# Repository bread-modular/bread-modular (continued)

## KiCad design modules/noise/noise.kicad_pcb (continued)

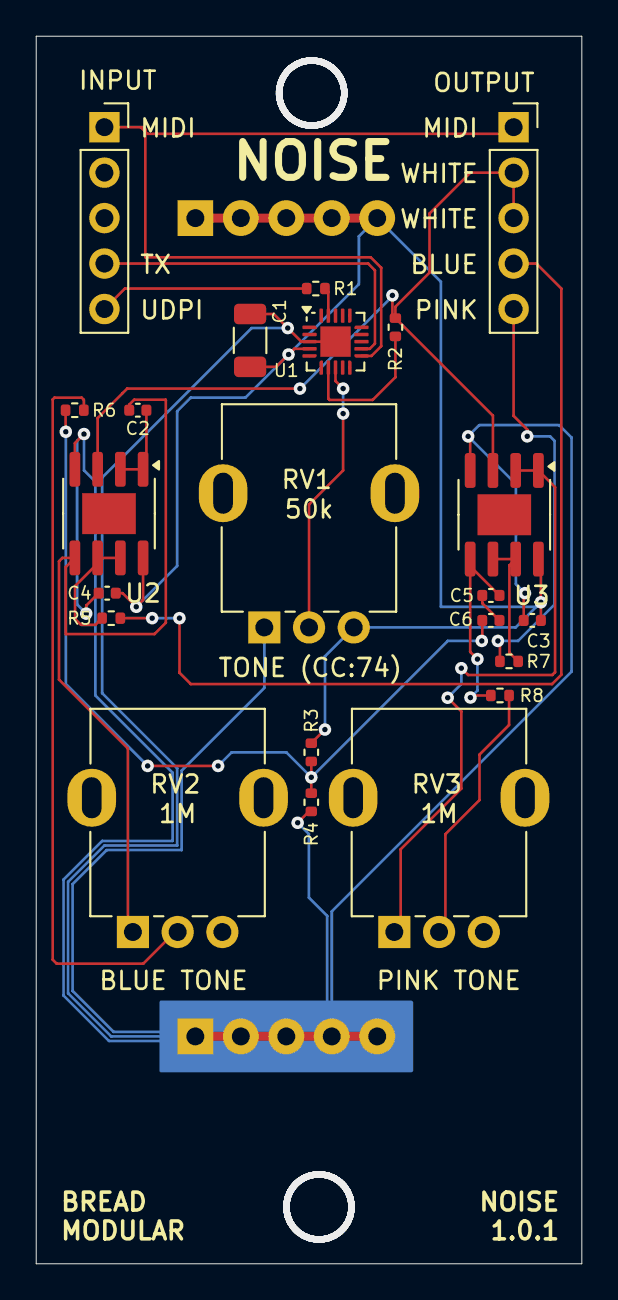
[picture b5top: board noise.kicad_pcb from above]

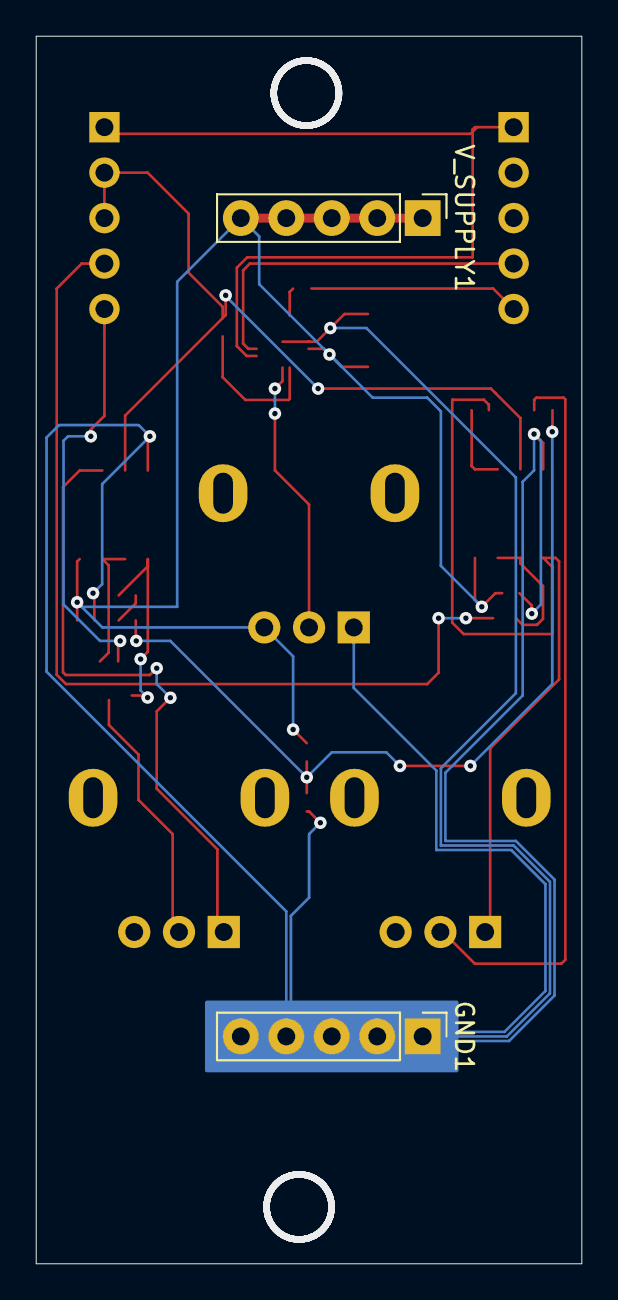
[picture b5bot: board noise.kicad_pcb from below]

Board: 2 copper layers, 30.5 x 68.6 mm, 24 parts (2 on the bottom side), 21 nets.

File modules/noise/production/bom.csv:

Designator,Footprint,Quantity,Value,LCSC Part #
C1,1206,1,100uf,
C2,0402,1,100pf,
"C3, C4",0402,2,100nf,
"C5, C6",0402,2,10nf,
"GND1, V_SUPPLY1",Power_Connector,2,Conn_01x05_Pin,
"INPUT1, OUTPUT1",PinSocket_1x05_P2.54mm_Vertical,2,Conn_01x05_Socket,
R1,0402,1,4.7k,
"R2, R3, R4, R5, R7",0402,5,1k,
R6,0402,1,330,
R8,0402,1,22k,
RV1,Potentiometer_RV09,1,50k,
"RV2, RV3",Potentiometer_RV09,2,1M,
U1,VQFN-20-1EP_3x3mm_P0.4mm_EP1.7x1.7mm,1,ATtiny1616-M,
"U2, U3",SOIC-8-1EP_3.9x4.9mm_P1.27mm_EP2.29x3mm,2,MCP6002-xSN,

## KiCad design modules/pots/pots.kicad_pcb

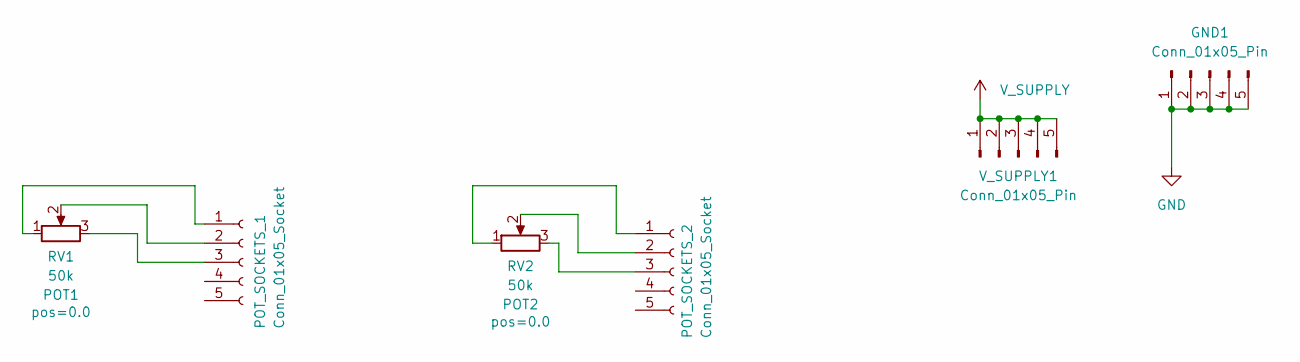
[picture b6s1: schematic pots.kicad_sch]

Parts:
GND1: Conn_01x05_Pin; Power_Connector
POT_SOCKETS_1, POT_SOCKETS_2: Conn_01x05_Socket; PinSocket_1x05_P2.54mm_Vertical
RV1, RV2: 50k; Potentiometer_RV09
V_SUPPLY1: Conn_01x05_Pin; Power_Connector

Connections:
GND: GND1.1, GND1.2, GND1.3, GND1.4, GND1.5
unnamed: POT_SOCKETS_1.1, RV1.1
unnamed: POT_SOCKETS_1.2, RV1.2
unnamed: POT_SOCKETS_1.3, RV1.3
unnamed: POT_SOCKETS_2.1, RV2.1
unnamed: POT_SOCKETS_2.2, RV2.2
unnamed: POT_SOCKETS_2.3, RV2.3
V_SUPPLY: V_SUPPLY1.1, V_SUPPLY1.2, V_SUPPLY1.3, V_SUPPLY1.4, V_SUPPLY1.5

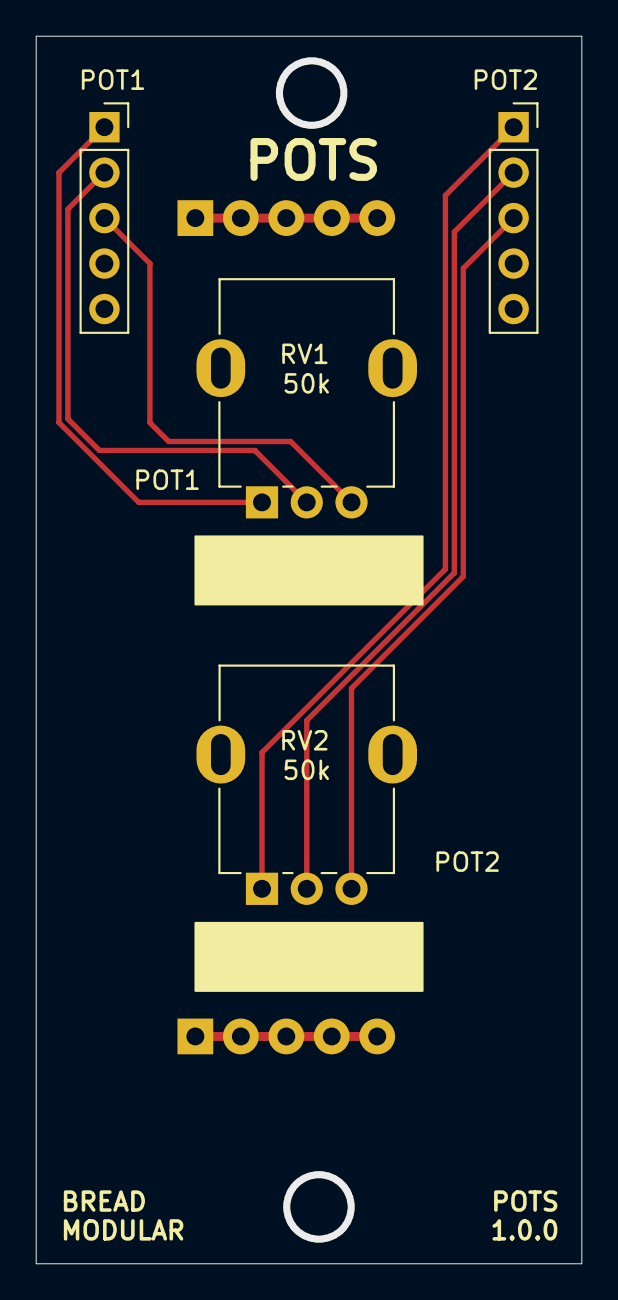
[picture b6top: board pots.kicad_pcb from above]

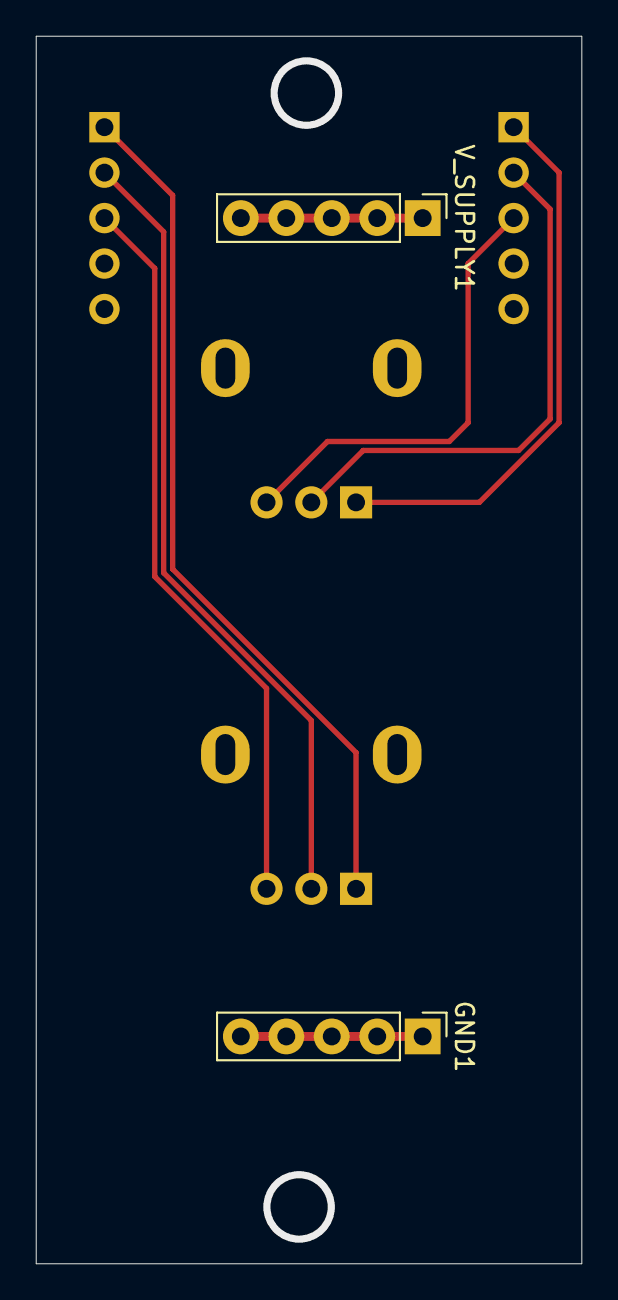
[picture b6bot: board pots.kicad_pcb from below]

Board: 2 copper layers, 30.5 x 68.6 mm, 6 parts (2 on the bottom side), 8 nets.

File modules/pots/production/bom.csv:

Designator,Footprint,Quantity,Value,LCSC Part #
"GND1, V_SUPPLY1",Power_Connector,2,Conn_01x05_Pin,
"POT_SOCKETS_1, POT_SOCKETS_2",PinSocket_1x05_P2.54mm_Vertical,2,Conn_01x05_Socket,
"RV1, RV2",Potentiometer_RV09,2,50k,

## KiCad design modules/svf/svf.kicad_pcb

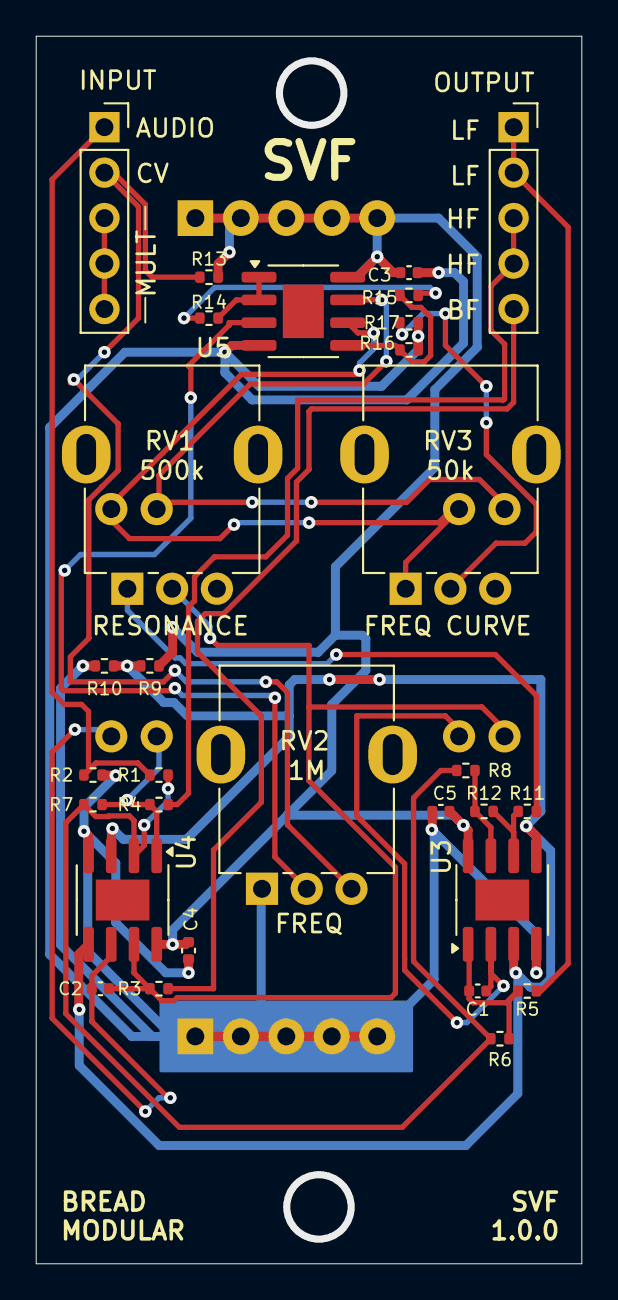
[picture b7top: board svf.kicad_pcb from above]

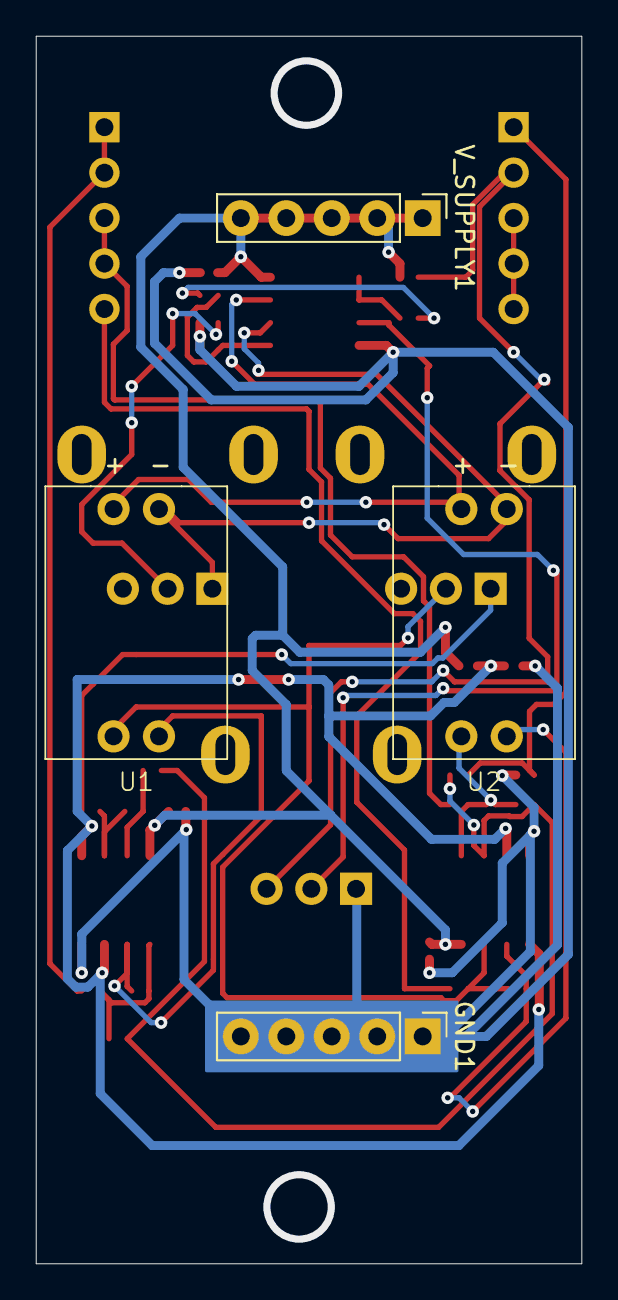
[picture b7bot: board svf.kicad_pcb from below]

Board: 2 copper layers, 30.5 x 68.6 mm, 34 parts (4 on the bottom side), 25 nets.

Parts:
C1, C2: 10nf; C_0402_1005Metric
C3, C4, C5: 0.1uf; C_0402_1005Metric
GND1: Conn_01x05_Pin; Power_Connector
INPUT1: Conn_01x05_Socket; PinSocket_1x05_P2.54mm_Vertical
OUTPUT1: Conn_01x05_Socket; PinSocket_1x05_P2.54mm_Vertical
R1, R11, R12: 51k; R_0402_1005Metric
R2: 22k; R_0402_1005Metric
R3, R4, R5, R9, R10, R14: 1k; R_0402_1005Metric
R6, R7, R8: 10k; R_0402_1005Metric
R13: 100k; R_0402_1005Metric
R15, R16: 1M; R_0402_1005Metric
R17: 5.1k; R_0402_1005Metric
RV1: 500k; Potentiometer_RV09
RV2: 1M; Potentiometer_RV09
RV3: 50k; Potentiometer_RV09
U1, U2: VTL5C
U3, U4, U5: MCP6002-xSN; SOIC-8-1EP_3.9x4.9mm_P1.27mm_EP2.29x3mm
V_SUPPLY1: Conn_01x05_Pin; Power_Connector

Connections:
GND: C3.2, C4.2, C5.2, GND1.1, GND1.2, GND1.3, GND1.4, GND1.5, R2.1, R10.2, R16.1, R17.1, RV2.1, U3.4 (V-), U4.4 (V-), U5.4 (V-)
unnamed: C1.2, R5.1, R6.1, U3.1
unnamed: C2.2, R3.1, RV1.2, U1.4, U4.7
unnamed: INPUT1.3, INPUT1.4, INPUT1.5
unnamed: R4.1, R7.2, U2.4, U4.1
unnamed: R11.2, RV1.1
unnamed: R8.1, R12.1, U3.7
unnamed: R14.1, R15.2
unnamed: R17.2, RV3.2
unnamed: C1.1, U1.3, U3.2 (-)
unnamed: R11.1, R12.2, U3.6 (-)
unnamed: R1.2, R6.2, R7.1, R8.2, U4.2 (-)
unnamed: C2.1, U2.3, U4.6 (-)
unnamed: RV2.2, U5.3 (+)
unnamed: R14.2, U5.1, U5.2 (-)
unnamed: R15.1, R16.2, U5.5 (+)
VACTROL_NEG: RV3.1, U1.1 (-), U2.1 (-), U5.6 (-)
VACTROL_POS: U1.2 (+), U2.2 (+), U5.7
V_BF: OUTPUT1.5, R3.2
V_CV: INPUT1.2, R13.1, RV2.3
V_HF: OUTPUT1.3, OUTPUT1.4, R4.2
V_IN: INPUT1.1, R1.1, R2.2
V_LF: OUTPUT1.1, OUTPUT1.2, R5.2
V_MID: R9.2, R10.1, U3.3 (+), U3.5 (+), U4.3 (+), U4.5 (+)
V_SUPPLY: C3.1, C4.1, C5.1, R9.1, R13.2, U3.8 (V+), U4.8 (V+), U5.8 (V+), V_SUPPLY1.1, V_SUPPLY1.2, V_SUPPLY1.3, V_SUPPLY1.4, V_SUPPLY1.5

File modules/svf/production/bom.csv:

Designator,Footprint,Quantity,Value,LCSC Part #
"C1, C2",0402,2,10nf,
"C3, C4, C5",0402,3,0.1uf,
"GND1, V_SUPPLY1",Power_Connector,2,Conn_01x05_Pin,
"INPUT1, OUTPUT1",PinSocket_1x05_P2.54mm_Vertical,2,Conn_01x05_Socket,
"R1, R11, R12",0402,3,51k,
"R10, R14, R3, R4, R5, R9",0402,6,1k,
R13,0402,1,100k,
"R15, R16",0402,2,1M,
R17,0402,1,5.1k,
R2,0402,1,22k,
"R6, R7, R8",0402,3,10k,
RV1,Potentiometer_RV09,1,500k,
RV2,Potentiometer_RV09,1,1M,
RV3,Potentiometer_RV09,1,50k,
"U1, U2",VTL5C,2,VTL5C,
"U3, U4, U5",SOIC-8-1EP_3.9x4.9mm_P1.27mm_EP2.29x3mm,3,MCP6002-xSN,

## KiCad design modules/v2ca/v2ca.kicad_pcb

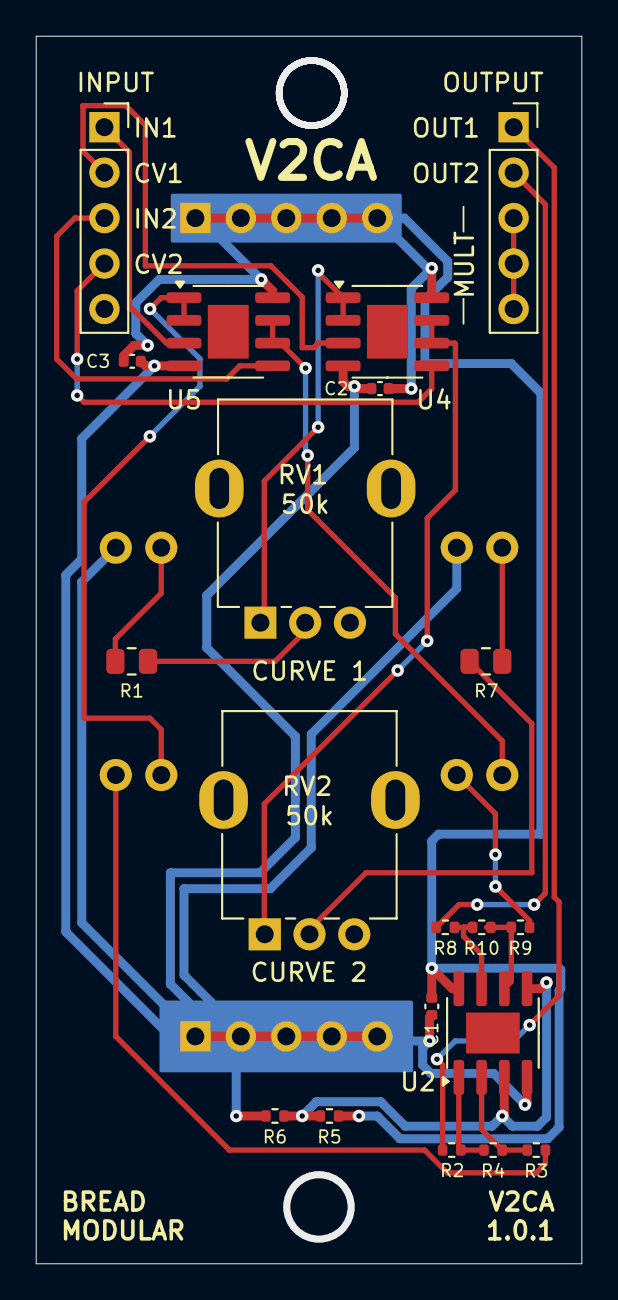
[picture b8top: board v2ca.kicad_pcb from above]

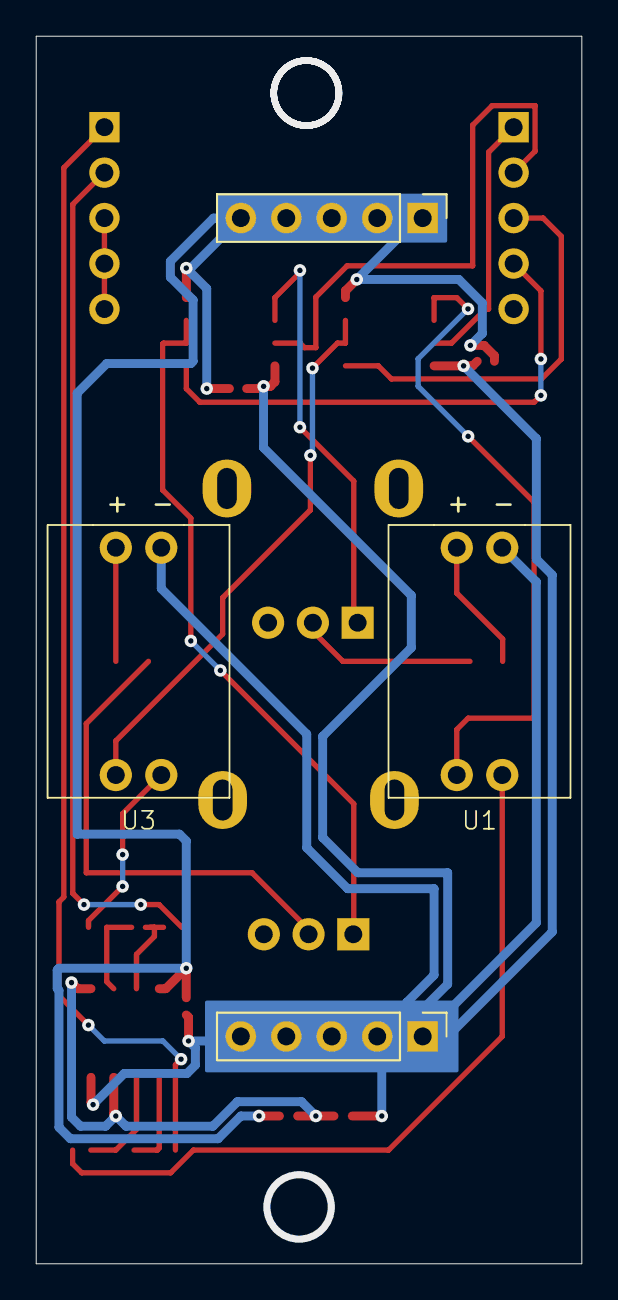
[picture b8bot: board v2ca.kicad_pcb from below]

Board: 2 copper layers, 30.5 x 68.6 mm, 24 parts (4 on the bottom side), 24 nets.

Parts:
5V1: Conn_01x05_Pin; PinHeader_1x05_P2.54mm_Vertical
C1, C2, C3: 0.1uf; C_0402_1005Metric
GND1: Conn_01x05_Pin; PinHeader_1x05_P2.54mm_Vertical
INPUT1: Conn_01x05_Socket; PinSocket_1x05_P2.54mm_Vertical
OUTPUT1: Conn_01x05_Socket; PinSocket_1x05_P2.54mm_Vertical
R1, R7: 330; R_0805_2012Metric
R2, R5, R6, R8: 1k; R_0402_1005Metric
R3, R4, R9, R10: 10k; R_0402_1005Metric
RV1, RV2: 50k; Potentiometer_RV09
U1, U3: VTL5C
U2, U4, U5: MCP6002-xSN; SOIC-8-1EP_3.9x4.9mm_P1.27mm_EP2.29x3mm

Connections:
+2.5V: R5.2, R6.1, U2.3 (+), U2.5 (+)
+5V: 5V1.1, 5V1.2, 5V1.3, 5V1.4, 5V1.5, C1.1, C2.1, C3.1, R5.1, U2.8 (V+), U4.8 (V+), U5.8 (V+)
CV1_IN: INPUT1.2, U4.3 (+)
CV2_IN: INPUT1.4, U4.5 (+)
GND: C1.2, C2.2, C3.2, GND1.1, GND1.2, GND1.3, GND1.4, GND1.5, R6.2, U1.1 (-), U2.4 (V-), U3.1 (-), U4.4 (V-), U5.4 (V-)
unnamed: OUTPUT1.3, OUTPUT1.4, OUTPUT1.5
unnamed: R1.1, RV1.2
unnamed: R2.1, R4.2, U2.1
unnamed: R3.1, U1.3
unnamed: R7.1, RV2.2
unnamed: R9.1, U3.3
unnamed: R8.1, R10.2, U2.7
unnamed: R1.2, U1.2 (+)
unnamed: R3.2, R4.1, U2.2 (-)
unnamed: R9.2, R10.1, U2.6 (-)
unnamed: R7.2, U3.2 (+)
unnamed: RV1.1, U4.1, U4.2 (-)
unnamed: RV2.1, U4.6 (-), U4.7
unnamed: U1.4, U5.1, U5.2 (-)
unnamed: U3.4, U5.6 (-), U5.7
V1_IN: INPUT1.1, U5.3 (+)
V1_OUT: OUTPUT1.1, R2.2
V2_IN: INPUT1.3, U5.5 (+)
V2_OUT: OUTPUT1.2, R8.2

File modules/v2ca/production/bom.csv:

Designator,Footprint,Quantity,Value,LCSC Part #
"5V1, GND1",PinHeader_1x05_P2.54mm_Vertical,2,Conn_01x05_Pin,
"C1, C2, C3",0402,3,0.1uf,
"INPUT1, OUTPUT1",PinSocket_1x05_P2.54mm_Vertical,2,Conn_01x05_Socket,
"R1, R7",0805,2,330,
"R10, R3, R4, R9",0402,4,10k,
"R2, R5, R6, R8",0402,4,1k,
"RV1, RV2",Potentiometer_RV09,2,50k,
"U1, U3",VTL5C,2,VTL5C,
"U2, U4, U5",SOIC-8-1EP_3.9x4.9mm_P1.27mm_EP2.29x3mm,3,MCP6002-xSN,
